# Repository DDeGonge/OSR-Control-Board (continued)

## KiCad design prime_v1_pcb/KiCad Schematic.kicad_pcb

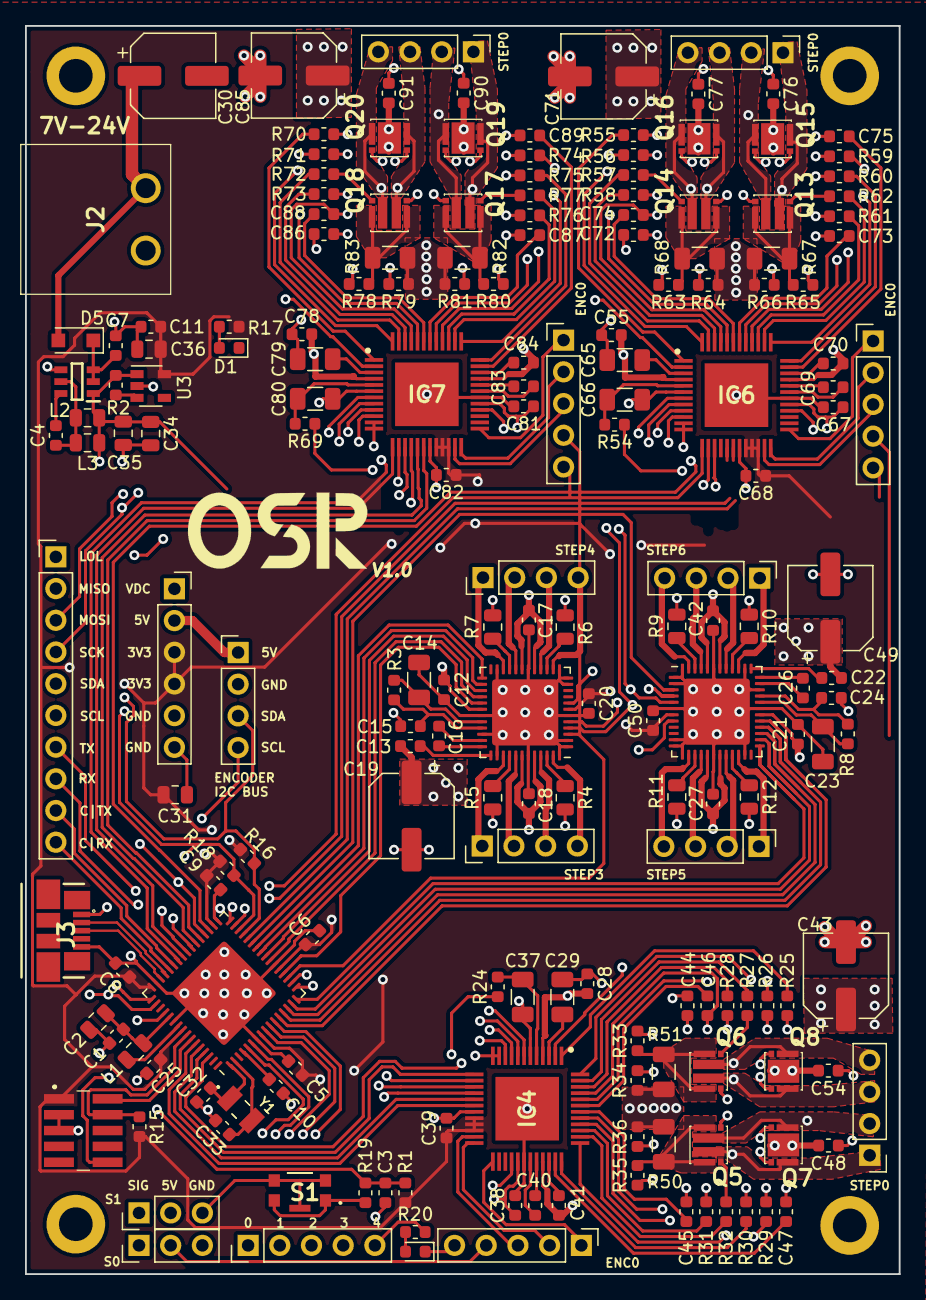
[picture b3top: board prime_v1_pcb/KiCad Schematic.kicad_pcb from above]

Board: 4 copper layers, 70.0 x 100.0 mm, 193 parts (0 on the bottom side), 212 nets.

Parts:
C1, C4, C5, C6, C8, C9, C12, C13, C17, C18, C20, C21, C22, C25, C27, C28, C39, C41, C42, C50, C55, C68, C70, C78, C82, C84: 100nF; C_0603_1608Metric
C2, C31, C34, C35, C36: 10uF; C_0805_2012Metric
C3, C7, C10, C11: 1uF; C_0603_1608Metric
C14, C23, C29, C37, C65, C66, C79, C80: 2.2uF; C_1206_3216Metric
C15, C24, C38, C48, C54, C67, C76, C77, C81, C90, C91: 470nF; C_0603_1608Metric
C16, C26, C40, C69, C83: 22nF; C_0603_1608Metric
C19, C30, C43, C49, C71, C85: 47uF; CP_Elec_6.3x7.7
C32, C33: 12pF; C_0603_1608Metric
C44, C45, C46, C47, C72, C73, C74, C75, C86, C87, C88, C89: 220nF; C_0603_1608Metric
D1, D2: LED; LED_0603_1608Metric
D5: CGRTS4004-HF; D_SOD-123F
IC1: AP63205WU-7; SOT95P280X100-6N
IC2: ATSAMD51J19A-MU; QFN-64-1EP_9x9mm_P0.5mm_EP6x6mm
IC4, IC6, IC7: TMC5160A-TA-T; QFP50P900X900X120-49N
J1, J4, J5, J7, J9, J14, J23, J24: Conn_01x04; PinHeader_1x04_P2.54mm_Vertical
J2: 691313710002
J3: 47346-0001
J6: 20021121-00010C4LF; 2002112100010C4LF
J8, J25, J26, J27: Conn_01x05; PinHeader_1x05_P2.54mm_Vertical
J13: Conn_01x10; PinHeader_1x10_P2.54mm_Vertical
J15, J16: Conn_01x03; PinHeader_1x03_P2.54mm_Vertical
J17, J18, J19, J20: Hole; MountingHole_2.7mm_M2.5_DIN965_Pad
J22: Conn_01x06; PinSocket_1x06_P2.54mm_Vertical
L1, L2, L3: 10uH; L_0805_2012Metric
Q5, Q6, Q7, Q8, Q13, Q14, Q15, Q16, Q17, Q18, Q19, Q20: FDMC8030; FDMC89521L
R1, R2, R15: 10k; R_0603_1608Metric
R3, R8, R24, R54, R69: 2R2; R_0603_1608Metric
R4, R5, R6, R7, R9, R10, R11, R12: 0R2; R_0805_2012Metric
R16, R18: 2k2; R_0603_1608Metric
R17, R19, R20: 174; R_0603_1608Metric
R25, R26, R27, R28, R29, R30, R31, R32, R55, R56, R57, R58, R59, R60, R61, R62, R70, R71, R72, R73, R74, R75, R76, R77: 15; R_0603_1608Metric
R33, R34, R35, R36, R63, R64, R65, R66, R78, R79, R80, R81: 47; R_0603_1608Metric
R50, R51, R67, R68, R82, R83: 0R05; R_1206_3216Metric
S1: KMR243GLFG; KMR421GULCLFS
U1, U2: TMC2041-LA; QFN-48-1EP_7x7mm_P0.5mm_EP5.3x5.3mm
U3: AP2112K-3.3; SOT-23-5
Y1: LFXTAL009678REEL

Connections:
+3V3: C5.1, C6.1, C8.1, C9.1, C11.1, C20.1, C25.1, C31.1, C36.1, C39.2, C50.1, C68.2, C82.2, IC2.8, IC2.21, IC2.34, IC2.48, IC2.56, IC4.20, IC4.21, IC4.22, IC6.20, IC6.21, IC6.22, IC7.20, IC7.21, IC7.22, J6.1, J22.3, J22.4, R1.1, R15.1, R16.1, R17.2, R18.1, U1.7, U2.7, U3.5
+5V: C34.1, C35.1, IC1.1, J3.1, J9.1, J15.2, J16.2, J22.2, J25.4, J26.4, J27.4, L2.1, L3.1, R2.1, U3.1
+VDC: C12.1, C13.1, C17.1, C18.1, C19.1, C21.1, C22.1, C27.1, C28.2, C30.1, C41.1, C42.1, C43.1, C48.2, C49.1, C54.2, C55.2, C70.1, C71.1, C76.2, C77.2, C78.2, C84.1, C85.1, C90.2, C91.2, D5.2, IC4.4, IC4.33, IC6.4, IC6.33, IC7.4, IC7.33, J2.1, J22.1, Q7.9, Q7.10, Q8.9, Q8.10, Q15.9, Q15.10, Q16.9, Q16.10, Q19.9, Q19.10, Q20.9, Q20.10, U1.17, U1.19, U1.30, U1.42, U1.44, U2.17, U2.19, U2.30, U2.42, U2.44
/2014Driver/5VO: C14.2, R3.1, U1.32
/2014Driver/BR1A: R4.1, U1.46
/2014Driver/BR1B: R5.1, U1.40
/2014Driver/BR2A: R6.1, U1.15
/2014Driver/BR2B: R7.1, U1.21
/2014Driver/S1_1A: J1.4, U1.47
/2014Driver/S1_1B: J1.2, U1.41
/2014Driver/S1_2A: J1.3, U1.45
/2014Driver/S1_2B: J1.1, U1.39
/2014Driver/S2_1A: J4.4, U1.14
/2014Driver/S2_1B: J4.2, U1.20
/2014Driver/S2_2A: J4.3, U1.16
/2014Driver/S2_2B: J4.1, U1.22
/2014Driver/VCC: C15.1, R3.2, U1.33
/2014Driver/VCP: C13.2, U1.37
/5160Driver0/D0_5VO: C37.2, IC4.5, R24.1
/5160Driver0/D0_12VO: C29.2, IC4.3
/5160Driver0/D0_ENCA: IC4.24, J25.2
/5160Driver0/D0_ENCB: IC4.23, J25.3
/5160Driver0/D0_ENCN: IC4.25, J25.1
/5160Driver0/D0_VCC: C38.1, IC4.29, R24.2
/5160Driver0/S0_1A: C45.1, IC4.40, J14.1, Q5.9, Q7.2, Q7.3, Q7.4
/5160Driver0/S0_1B: C44.1, IC4.48, J14.3, Q6.9, Q8.2, Q8.3, Q8.4
/5160Driver0/S0_2A: C47.1, IC4.37, J14.2, Q5.10, Q7.5, Q7.6, Q7.7
/5160Driver0/S0_2B: C46.1, IC4.45, J14.4, Q6.10, Q8.5, Q8.6, Q8.7
/5160Driver0/S0_HA1: Q7.1, R29.2
/5160Driver0/S0_HA2: Q7.8, R30.1
/5160Driver0/S0_HB1: Q8.1, R25.2
/5160Driver0/S0_HB2: Q8.8, R26.1
/5160Driver0/S0_LA1: Q5.1, R31.2
/5160Driver0/S0_LA2: Q5.8, R32.1
/5160Driver0/S0_LB1: Q6.1, R27.2
/5160Driver0/S0_LB2: Q6.8, R28.1
/5160Driver0/S0_SRAH: Q5.2, Q5.3, Q5.4, Q5.5, Q5.6, Q5.7, R35.2, R50.1
/5160Driver0/S0_SRBH: Q6.2, Q6.3, Q6.4, Q6.5, Q6.6, Q6.7, R33.2, R51.1
/AREF: C10.1, IC2.4
/CAN_RX: IC2.44, J13.10
/CAN_TX: IC2.43, J13.9
/D0_CS: IC2.61, IC4.13
/D0_DIR: IC2.59, IC4.18
/D0_EN: IC2.62, IC4.28
/D0_STEP: IC2.60, IC4.17
/D1_CS: IC2.32, IC6.13
/D1_DIR: IC2.28, IC6.18
/D1_EN: IC2.35, IC6.28
/D1_STEP: IC2.31, IC6.17
/D2_CS: IC2.41, IC7.13
/D2_DIR: IC2.37, IC7.18
/D2_EN: IC2.42, IC7.28
/D2_STEP: IC2.38, IC7.17
/D3D4_CS: IC2.19, U1.3
/D3D4_EN: IC2.20, U1.29
/D3_DIR: IC2.24, U1.27
/D3_STEP: IC2.23, U1.28
/D4_DIR: IC2.26, U1.25
/D4_STEP: IC2.25, U1.26
/D5D6_CS: IC2.27, U2.3
/D5D6_EN: IC2.12, U2.29
/D5_DIR: IC2.14, U2.27
/D5_STEP: IC2.13, U2.28
/D6_DIR: IC2.16, U2.25
/D6_STEP: IC2.15, U2.26
/D+: IC2.46, J3.3
/D-: IC2.45, J3.2
/GPIO1: IC2.5, J8.1
/GPIO2: IC2.6, J8.2
/GPIO3: IC2.9, J8.3
/GPIO4: IC2.10, J8.4
/GPIO5: IC2.11, J8.5, R20.2
/MISO: IC2.49, IC4.16, IC6.16, IC7.16, J13.2, U1.8, U2.8
/MOSI: IC2.50, IC4.15, IC6.15, IC7.15, J13.3, U1.5, U2.5
/OSC0: C32.2, IC2.1, Y1.1
/OSC1: C33.1, IC2.2, Y1.2
/RESET: C3.1, IC2.52, J6.10, R1.2, R19.2
/RX: IC2.40, J13.8
/SCK: IC2.36, IC4.14, IC6.14, IC7.14, J13.4, U1.4, U2.4
/SCL: IC2.30, J9.4, J13.6, R18.2
/SDA: IC2.29, J9.3, J13.5, R16.2
/SERVO0: IC2.17, J16.1
/SERVO1: IC2.18, J15.1
/SWCLK: IC2.57, J6.4, R15.2
/SWDIO: IC2.58, J6.2
/TX: IC2.39, J13.7
/VDDCORE: C1.1, C2.1, IC2.53, L1.2
/VSW: IC2.55, L1.1
/sheet60C9AE4D/5VO: C23.2, R8.1, U2.32
/sheet60C9AE4D/BR1A: R9.1, U2.46
/sheet60C9AE4D/BR1B: R10.1, U2.40
/sheet60C9AE4D/BR2A: R11.1, U2.15
/sheet60C9AE4D/BR2B: R12.1, U2.21
/sheet60C9AE4D/S1_1A: J5.4, U2.47
/sheet60C9AE4D/S1_1B: J5.2, U2.41
/sheet60C9AE4D/S1_2A: J5.3, U2.45
/sheet60C9AE4D/S1_2B: J5.1, U2.39
/sheet60C9AE4D/S2_1A: J7.4, U2.14
/sheet60C9AE4D/S2_1B: J7.2, U2.20
/sheet60C9AE4D/S2_2A: J7.3, U2.16
/sheet60C9AE4D/S2_2B: J7.1, U2.22
/sheet60C9AE4D/VCC: C24.1, R8.2, U2.33
/sheet60C9AE4D/VCP: C22.2, U2.37
/sheet61BB23C4/D0_5VO: C66.2, IC6.5, R54.1
/sheet61BB23C4/D0_12VO: C65.2, IC6.3
/sheet61BB23C4/D0_ENCA: IC6.24, J26.2
/sheet61BB23C4/D0_ENCB: IC6.23, J26.3
/sheet61BB23C4/D0_ENCN: IC6.25, J26.1
/sheet61BB23C4/D0_VCC: C67.1, IC6.29, R54.2
/sheet61BB23C4/S0_1A: C73.1, IC6.40, J23.1, Q13.9, Q15.2, Q15.3, Q15.4
/sheet61BB23C4/S0_1B: C72.1, IC6.48, J23.3, Q14.9, Q16.2, Q16.3, Q16.4
/sheet61BB23C4/S0_2A: C75.1, IC6.37, J23.2, Q13.10, Q15.5, Q15.6, Q15.7
/sheet61BB23C4/S0_2B: C74.1, IC6.45, J23.4, Q14.10, Q16.5, Q16.6, Q16.7
/sheet61BB23C4/S0_HA1: Q15.1, R59.2
/sheet61BB23C4/S0_HA2: Q15.8, R60.1
/sheet61BB23C4/S0_HB1: Q16.1, R55.2
/sheet61BB23C4/S0_HB2: Q16.8, R56.1
/sheet61BB23C4/S0_LA1: Q13.1, R61.2
/sheet61BB23C4/S0_LA2: Q13.8, R62.1
/sheet61BB23C4/S0_LB1: Q14.1, R57.2
/sheet61BB23C4/S0_LB2: Q14.8, R58.1
/sheet61BB23C4/S0_SRAH: Q13.2, Q13.3, Q13.4, Q13.5, Q13.6, Q13.7, R65.2, R67.1
/sheet61BB23C4/S0_SRBH: Q14.2, Q14.3, Q14.4, Q14.5, Q14.6, Q14.7, R63.2, R68.1
/sheet61C22781/D0_5VO: C80.2, IC7.5, R69.1
/sheet61C22781/D0_12VO: C79.2, IC7.3
/sheet61C22781/D0_ENCA: IC7.24, J27.2
/sheet61C22781/D0_ENCB: IC7.23, J27.3
/sheet61C22781/D0_ENCN: IC7.25, J27.1
/sheet61C22781/D0_VCC: C81.1, IC7.29, R69.2
/sheet61C22781/S0_1A: C87.1, IC7.40, J24.1, Q17.9, Q19.2, Q19.3, Q19.4
/sheet61C22781/S0_1B: C86.1, IC7.48, J24.3, Q18.9, Q20.2, Q20.3, Q20.4
/sheet61C22781/S0_2A: C89.1, IC7.37, J24.2, Q17.10, Q19.5, Q19.6, Q19.7
/sheet61C22781/S0_2B: C88.1, IC7.45, J24.4, Q18.10, Q20.5, Q20.6, Q20.7
/sheet61C22781/S0_HA1: Q19.1, R74.2
/sheet61C22781/S0_HA2: Q19.8, R75.1
/sheet61C22781/S0_HB1: Q20.1, R70.2
/sheet61C22781/S0_HB2: Q20.8, R71.1
/sheet61C22781/S0_LA1: Q17.1, R76.2
/sheet61C22781/S0_LA2: Q17.8, R77.1
/sheet61C22781/S0_LB1: Q18.1, R72.2
/sheet61C22781/S0_LB2: Q18.8, R73.1
/sheet61C22781/S0_SRAH: Q17.2, Q17.3, Q17.4, Q17.5, Q17.6, Q17.7, R80.2, R82.1
/sheet61C22781/S0_SRBH: Q18.2, Q18.3, Q18.4, Q18.5, Q18.6, Q18.7, R78.2, R83.1
GND: C1.2, C2.2, C3.2, C5.2, C6.2, C7.2, C8.2, C9.2, C10.2, C11.2, C12.2, C14.1, C15.2, C17.2, C18.2, C19.2, C20.2, C21.2, C23.1, C24.2, C25.2, C27.2, C28.1, C29.1, C30.2, C31.2, C32.1, C33.2, C34.2, C35.2, C36.2, C37.1, C38.2, C39.1, C42.2, C43.2, C48.1, C49.2, C50.2, C54.1, C55.1, C65.1, C66.1, C67.2, C68.1, C71.2, C76.1, C77.1, C78.1, C79.1, C80.1, C81.2, C82.1, C85.2, C90.1, C91.1, D1.1, D2.1, IC1.4, IC2.7, IC2.22, IC2.33, IC2.47, IC2.54, IC2.65, IC4.6, IC4.11, IC4.12, IC4.19, IC4.30, IC4.49, IC6.6, IC6.11, IC6.12, IC6.19, IC6.30, IC6.49, IC7.6, IC7.11, IC7.12, IC7.19, IC7.30, IC7.49, J2.2, J3.5, J6.3, J6.5, J9.2, J15.3, J16.3, J17.1, J18.1, J19.1, J20.1, J22.5, J22.6, J25.5, J26.5, J27.5, R4.2, R5.2, R6.2, R7.2, R9.2, R10.2, R11.2, R12.2, R34.1, R36.1, R50.2, R51.2, R64.1, R66.1, R67.2, R68.2, R79.1, R81.1, R82.2, R83.2, S1.2, S1.3, S1.5, U1.1, U1.2, U1.6, U1.11, U1.12, U1.13, U1.18, U1.23, U1.31, U1.34, U1.38, U1.43, U1.48, U1.49, U2.1, U2.2, U2.6, U2.11, U2.12, U2.13, U2.18, U2.23, U2.31, U2.34, U2.38, U2.43, U2.48, U2.49, U3.2
unnamed: C4.1, IC1.5, L2.2, L3.2
unnamed: C4.2, IC1.6
unnamed: C7.1, D5.1, IC1.2, IC1.3
unnamed: C16.1, U1.36
unnamed: C16.2, U1.35
unnamed: C26.1, U2.36
unnamed: C26.2, U2.35
unnamed: C40.1, IC4.32
unnamed: C40.2, IC4.31
unnamed: C41.2, IC4.34
unnamed: C44.2, IC4.2
unnamed: C45.2, IC4.42
unnamed: C46.2, IC4.43
unnamed: C47.2, IC4.35
unnamed: C69.1, IC6.32
unnamed: C69.2, IC6.31
unnamed: C70.2, IC6.34
unnamed: C72.2, IC6.2
unnamed: C73.2, IC6.42
unnamed: C74.2, IC6.43
unnamed: C75.2, IC6.35
unnamed: C83.1, IC7.32
unnamed: C83.2, IC7.31
unnamed: C84.2, IC7.34
unnamed: C86.2, IC7.2
unnamed: C87.2, IC7.42
unnamed: C88.2, IC7.43
unnamed: C89.2, IC7.35
unnamed: D1.2, R17.1
unnamed: D2.2, R20.1
unnamed: IC4.1, R25.1
unnamed: IC4.7, R36.2
unnamed: IC4.8, R35.1
unnamed: IC4.9, R33.1
unnamed: IC4.10, R34.2
unnamed: IC4.36, R30.2
unnamed: IC4.38, R32.2
unnamed: IC4.39, R31.1
unnamed: IC4.41, R29.1
unnamed: IC4.44, R26.2
unnamed: IC4.46, R28.2
unnamed: IC4.47, R27.1
unnamed: IC6.1, R55.1
unnamed: IC6.7, R66.2
unnamed: IC6.8, R65.1
unnamed: IC6.9, R63.1
unnamed: IC6.10, R64.2
unnamed: IC6.36, R60.2
unnamed: IC6.38, R62.2
unnamed: IC6.39, R61.1
unnamed: IC6.41, R59.1
unnamed: IC6.44, R56.2
unnamed: IC6.46, R58.2
unnamed: IC6.47, R57.1
unnamed: IC7.1, R70.1
unnamed: IC7.7, R81.2
unnamed: IC7.8, R80.1
unnamed: IC7.9, R78.1
unnamed: IC7.10, R79.2
unnamed: IC7.36, R75.2
unnamed: IC7.38, R77.2
unnamed: IC7.39, R76.1
unnamed: IC7.41, R74.1
unnamed: IC7.44, R71.2
unnamed: IC7.46, R73.2
unnamed: IC7.47, R72.1
unnamed: R2.2, U3.3
unnamed: R19.1, S1.1, S1.4

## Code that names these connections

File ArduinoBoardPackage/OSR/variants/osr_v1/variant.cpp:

/*
  Copyright (c) 2014-2015 Arduino LLC.  All right reserved.

  This library is free software; you can redistribute it and/or
  modify it under the terms of the GNU Lesser General Public
  License as published by the Free Software Foundation; either
  version 2.1 of the License, or (at your option) any later version.

  This library is distributed in the hope that it will be useful,
  but WITHOUT ANY WARRANTY; without even the implied warranty of
  MERCHANTABILITY or FITNESS FOR A PARTICULAR PURPOSE.
  See the GNU Lesser General Public License for more details.

  You should have received a copy of the GNU Lesser General Public
  License along with this library; if not, write to the Free Software
  Foundation, Inc., 51 Franklin St, Fifth Floor, Boston, MA  02110-1301  USA
*/

#include "variant.h"

/*
 * Pins descriptions
 */

//TCC0 IOSET 6
//TCC1 IOSET 1
//TC0 IOSET 1
//TC1 IOSET 1
//TC2 IOSET 2
//TC3 IOSET 1
//TC4 IOSET 1
const PinDescription g_APinDescription[]=
{
  // 0..4 - Analog Pins
  { PORTB,  9, PIO_ANALOG, (PIN_ATTR_ANALOG|PIN_ATTR_PWM_E), ADC_Channel3, TC4_CH1, TC4_CH1, EXTERNAL_INT_9 },
  { PORTA,  4, PIO_ANALOG, (PIN_ATTR_ANALOG|PIN_ATTR_PWM_E), ADC_Channel4, TC0_CH0, TC0_CH0, EXTERNAL_INT_4 },
  { PORTA,  5, PIO_ANALOG, (PIN_ATTR_ANALOG|PIN_ATTR_PWM_E), ADC_Channel5, TC0_CH1, TC0_CH1, EXTERNAL_INT_5 },
  { PORTA,  6, PIO_ANALOG, (PIN_ATTR_ANALOG|PIN_ATTR_PWM_E), ADC_Channel6, TC1_CH0, TC1_CH0, EXTERNAL_INT_6 },
  { PORTA,  7, PIO_ANALOG, (PIN_ATTR_ANALOG|PIN_ATTR_PWM_E), ADC_Channel7, TC1_CH1, TC1_CH1, EXTERNAL_INT_7 },

  // 5..14 - Digital Pins
  { PORTA,  8, PIO_DIGITAL, PIN_ATTR_NONE, No_ADC_Channel, NOT_ON_PWM, NOT_ON_TIMER, EXTERNAL_INT_NONE },
  { PORTA,  9, PIO_DIGITAL, PIN_ATTR_NONE, No_ADC_Channel, NOT_ON_PWM, NOT_ON_TIMER, EXTERNAL_INT_NONE },
  { PORTA, 10, PIO_DIGITAL, PIN_ATTR_NONE, No_ADC_Channel, NOT_ON_PWM, NOT_ON_TIMER, EXTERNAL_INT_NONE },
  { PORTA, 11, PIO_DIGITAL, PIN_ATTR_NONE, No_ADC_Channel, NOT_ON_PWM, NOT_ON_TIMER, EXTERNAL_INT_NONE },
  { PORTB, 10, PIO_DIGITAL, PIN_ATTR_NONE, No_ADC_Channel, NOT_ON_PWM, NOT_ON_TIMER, EXTERNAL_INT_10 },
  { PORTB, 11, PIO_DIGITAL, PIN_ATTR_NONE, No_ADC_Channel, NOT_ON_PWM, NOT_ON_TIMER, EXTERNAL_INT_11 },
  { PORTB, 12, PIO_DIGITAL, PIN_ATTR_NONE, No_ADC_Channel, NOT_ON_PWM, NOT_ON_TIMER, EXTERNAL_INT_12 },
  { PORTB, 13, PIO_DIGITAL, PIN_ATTR_NONE, No_ADC_Channel, NOT_ON_PWM, NOT_ON_TIMER, EXTERNAL_INT_13 },
  { PORTB, 14, PIO_DIGITAL, PIN_ATTR_NONE, No_ADC_Channel, NOT_ON_PWM, NOT_ON_TIMER, EXTERNAL_INT_14 },
  { PORTB, 15, PIO_DIGITAL, PIN_ATTR_NONE, No_ADC_Channel, NOT_ON_PWM, NOT_ON_TIMER, EXTERNAL_INT_15 },

  // 15..16 - SERCOM/UART (Serial1)
  { PORTB, 17, PIO_SERCOM, PIN_ATTR_PWM_G, No_ADC_Channel, TCC0_CH4, NOT_ON_TIMER, EXTERNAL_INT_1 }, // RX: SERCOM5/PAD[1]
  { PORTB, 16, PIO_SERCOM, PIN_ATTR_PWM_G, No_ADC_Channel, TCC0_CH5, NOT_ON_TIMER, EXTERNAL_INT_0 }, // TX: SERCOM5/PAD[0]

  // 17..18 - Gates
  { PORTB, 7,  PIO_DIGITAL, PIN_ATTR_NONE, No_ADC_Channel, NOT_ON_PWM, NOT_ON_TIMER, EXTERNAL_INT_NONE }, // Gate 0
  { PORTB, 8,  PIO_DIGITAL, PIN_ATTR_NONE, No_ADC_Channel, NOT_ON_PWM, NOT_ON_TIMER, EXTERNAL_INT_NONE }, // Gate 1

  // 19..20 - I2C pins (SDA/SCL)
  { PORTA, 12, PIO_SERCOM, PIN_ATTR_PWM_E, No_ADC_Channel, TC2_CH0, TC2_CH0, EXTERNAL_INT_12 }, // SDA: SERCOM2/PAD[0]
  { PORTA, 13, PIO_SERCOM, PIN_ATTR_PWM_E, No_ADC_Channel, TC2_CH1, TC2_CH1, EXTERNAL_INT_13 }, // SCL: SERCOM2/PAD[1]

  // 21..23 - SPI pins (MISO,MOSI,SCK)
  { PORTB, 22, PIO_SERCOM, PIN_ATTR_DIGITAL, No_ADC_Channel, NOT_ON_PWM, NOT_ON_TIMER, EXTERNAL_INT_6 }, // MISO: SERCOM1/PAD[2]
  { PORTB, 23, PIO_SERCOM, PIN_ATTR_DIGITAL, No_ADC_Channel, NOT_ON_PWM, NOT_ON_TIMER, EXTERNAL_INT_7 }, // MOSI: SERCOM1/PAD[3]
  { PORTA, 17, PIO_SERCOM, PIN_ATTR_DIGITAL, No_ADC_Channel, NOT_ON_PWM, NOT_ON_TIMER, EXTERNAL_INT_1 }, // SCK: SERCOM1/PAD[1]

  // 24..26 - USB
  { NOT_A_PORT, 0, PIO_NOT_A_PIN, PIN_ATTR_NONE, No_ADC_Channel, NOT_ON_PWM, NOT_ON_TIMER, EXTERNAL_INT_NONE }, // USB Host enable DOES NOT EXIST ON THIS BOARD
  { PORTA, 24, PIO_COM, PIN_ATTR_NONE, No_ADC_Channel, NOT_ON_PWM, NOT_ON_TIMER, EXTERNAL_INT_NONE }, // USB/DM
  { PORTA, 27, PIO_COM, PIN_ATTR_NONE, No_ADC_Channel, NOT_ON_PWM, NOT_ON_TIMER, EXTERNAL_INT_NONE }, // USB/DP

  // 27 (AREF)
  { PORTA, 3, PIO_ANALOG, PIN_ATTR_ANALOG, No_ADC_Channel, NOT_ON_PWM, NOT_ON_TIMER, EXTERNAL_INT_NONE }, // DAC/VREFP

  // 28..33 - Stepper driver 0 pins
  { PORTB,  6, PIO_DIGITAL, PIN_ATTR_NONE, No_ADC_Channel, NOT_ON_PWM, NOT_ON_TIMER, EXTERNAL_INT_NONE },   // D0_CS
  { PORTB, 30, PIO_DIGITAL, PIN_ATTR_NONE, No_ADC_Channel, NOT_ON_PWM, NOT_ON_TIMER, EXTERNAL_INT_NONE },   // D0_EN
  { PORTB, 31, PIO_DIGITAL, PIN_ATTR_NONE, No_ADC_Channel, NOT_ON_PWM, NOT_ON_TIMER, EXTERNAL_INT_NONE },   // D0_S0_STEP
  { PORTB,  0, PIO_DIGITAL, PIN_ATTR_NONE, No_ADC_Channel, NOT_ON_PWM, NOT_ON_TIMER, EXTERNAL_INT_NONE },   // D0_S0_DIR
  { PORTB,  5, PIO_DIGITAL, PIN_ATTR_NONE, No_ADC_Channel, NOT_ON_PWM, NOT_ON_TIMER, EXTERNAL_INT_NONE },   // D0_S1_STEP
  { PORTB,  4, PIO_DIGITAL, PIN_ATTR_NONE, No_ADC_Channel, NOT_ON_PWM, NOT_ON_TIMER, EXTERNAL_INT_NONE },   // D0_S1_DIR

  // 34..39 - Stepper driver 1 pins
  { PORTA, 18, PIO_DIGITAL, PIN_ATTR_NONE, No_ADC_Channel, NOT_ON_PWM, NOT_ON_TIMER, EXTERNAL_INT_NONE },   // D1_CS
  { PORTA, 19, PIO_DIGITAL, PIN_ATTR_NONE, No_ADC_Channel, NOT_ON_PWM, NOT_ON_TIMER, EXTERNAL_INT_NONE },   // D1_EN
  { PORTA, 20, PIO_DIGITAL, PIN_ATTR_NONE, No_ADC_Channel, NOT_ON_PWM, NOT_ON_TIMER, EXTERNAL_INT_NONE },   // D1_S0_STEP
  { PORTA, 21, PIO_DIGITAL, PIN_ATTR_NONE, No_ADC_Channel, NOT_ON_PWM, NOT_ON_TIMER, EXTERNAL_INT_NONE },   // D1_S0_DIR
  { PORTA, 22, PIO_DIGITAL, PIN_ATTR_NONE, No_ADC_Channel, NOT_ON_PWM, NOT_ON_TIMER, EXTERNAL_INT_NONE },   // D1_S1_STEP
  { PORTA, 23, PIO_DIGITAL, PIN_ATTR_NONE, No_ADC_Channel, NOT_ON_PWM, NOT_ON_TIMER, EXTERNAL_INT_NONE },   // D1_S1_DIR

  // 40 - SD Chip Select
  { NOT_A_PORT, 0,  PIO_NOT_A_PIN, PIN_ATTR_NONE, No_ADC_Channel, NOT_ON_PWM, NOT_ON_TIMER, EXTERNAL_INT_NONE }, // OOPSIE

  // 41..43 - Servo Pins
  { PORTA, 16, PIO_DIGITAL, PIN_ATTR_NONE, No_ADC_Channel, NOT_ON_PWM, NOT_ON_TIMER, EXTERNAL_INT_NONE },   // Servo0
  { PORTA, 15, PIO_DIGITAL, PIN_ATTR_NONE, No_ADC_Channel, NOT_ON_PWM, NOT_ON_TIMER, EXTERNAL_INT_NONE },   // Servo1
  { PORTA, 14, PIO_DIGITAL, PIN_ATTR_NONE, No_ADC_Channel, NOT_ON_PWM, NOT_ON_TIMER, EXTERNAL_INT_NONE },   // Servo2
} ;

const void* g_apTCInstances[TCC_INST_NUM+TC_INST_NUM]={ TCC0, TCC1, TCC2, TCC3, TCC4, TC0, TC1, TC2, TC3, TC4, TC5 } ;
const uint32_t GCLK_CLKCTRL_IDs[TCC_INST_NUM+TC_INST_NUM] = { TCC0_GCLK_ID, TCC1_GCLK_ID, TCC2_GCLK_ID, TCC3_GCLK_ID, TCC4_GCLK_ID, TC0_GCLK_ID, TC1_GCLK_ID, TC2_GCLK_ID, TC3_GCLK_ID, TC4_GCLK_ID, TC5_GCLK_ID } ;

// Multi-serial objects instantiation
SERCOM sercom0( SERCOM0 ) ;
SERCOM sercom1( SERCOM1 ) ;
SERCOM sercom2( SERCOM2 ) ;
SERCOM sercom3( SERCOM3 ) ;
SERCOM sercom4( SERCOM4 ) ;
SERCOM sercom5( SERCOM5 ) ;

Uart Serial1( &sercom5, PIN_SERIAL1_RX, PIN_SERIAL1_TX, PAD_SERIAL1_RX, PAD_SERIAL1_TX ) ;

void SERCOM5_0_Handler()
{
  Serial1.IrqHandler();
}
void SERCOM5_1_Handler()
{
  Serial1.IrqHandler();
}
void SERCOM5_2_Handler()
{
  Serial1.IrqHandler();
}
void SERCOM5_3_Handler()
{
  Serial1.IrqHandler();
}

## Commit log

2020-10-04 v1.0 release
2020-10-09 rename folder for clarity. Versioning handled by git tags
2020-10-10 add power header
2020-10-21 wip building arduino configuration
2020-10-21 attempt to use board with arduino
2020-10-21 update url
2020-10-21 json parse fix
2020-10-21 json fixes
2020-10-21 whoops forgot this
2020-10-21 try md5 i guess
2020-10-21 update arduino board files, not done yet
2020-10-23 finally working arduino board config
2020-10-24 forgot libraries, bump version
2020-10-25 begin work on OSR library
2020-10-25 bugfixes and whatnot
2020-10-28 library bump
2020-10-28 im bad at c++ plz send help
2020-10-28 got the drivers working still some bugs
2020-10-30 major arduino driver library updates
2020-10-30 steppers 2 and 3 output were flopped
2020-10-31 tweaks
2020-10-31 arduino version bump
2020-11-01 skookum updates
2020-11-01 much improvements, very nice
2020-11-06 osr package bump
2020-11-12 library update, no version bump
2020-11-18 resolve a few issues in pcb design
2020-11-23 version bump
2020-12-03 pcb optimizations and fixes to v1 arduino package
2020-12-05 pcb v2 release
2021-01-29 package update for v2
2021-01-29 osr v2 package bugfix
2021-01-29 lol oops
2021-01-29 finally works yeeeee
2021-06-25 add new driver support and enable debug prints
2021-06-27 remove some debug delays from arduino library
2021-07-07 some work fixing board, bump arduino package version
2022-08-31 update prime board to v2
